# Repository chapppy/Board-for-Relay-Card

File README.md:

#  Board-for-Relay-Card
This repository contains design of schematic and PCB for Relay Card. 
**This board support**:
- up to 7 relays (with SPDT contacts)
- additional 7 relays on extra board
- control of relay over USB
- control of relay over CAN
- single power supply from USB
- possibility of external power supply (for board control over CAN)

This is based on STM32 microcontroller F0 family (STM32F072C8T6). This microcontroller supports USB and in advance it support crystal-less USB. The CAN driver is also available. 

The goal is use as less parts as possible with consideration of hand soldering. All the part should be simple to get or replace with another compatible. The design is simple two layer board with most of the parts (and all necessary) on top layer. The design fits to box for DIN lath.

This is related to these repositories:
[Firmware-for-Relay-Card](https://github.com/chapppy/Firmware-for-Relay-Card "Firmware-for-Relay-Card") 
[Sample-GUI-for-Relay-Card](https://github.com/chapppy/Sample-GUI-for-Relay-Card "Sample-GUI-for-Relay-Card")
[Board-for-Relay-Card](https://github.com/chapppy/Board-for-Relay-Card "Board-for-Relay-Card")

## schematic
[full schematic](https://github.com/chapppy/Board-for-Relay-Card/blob/master/export/schematic-full.pdf "full schematic")

In case of control only over USB and 4 relays, there is reduced schematic:
[reduced schematic](https://github.com/chapppy/Board-for-Relay-Card/blob/master/export/schematic-USB-4-rleays.pdf "reduced schematic")

## PCB design

## data for manufacturing
[manufacturing data](https://github.com/chapppy/Board-for-Relay-Card/blob/master/export/manufacturing.zip "manufacturing data")

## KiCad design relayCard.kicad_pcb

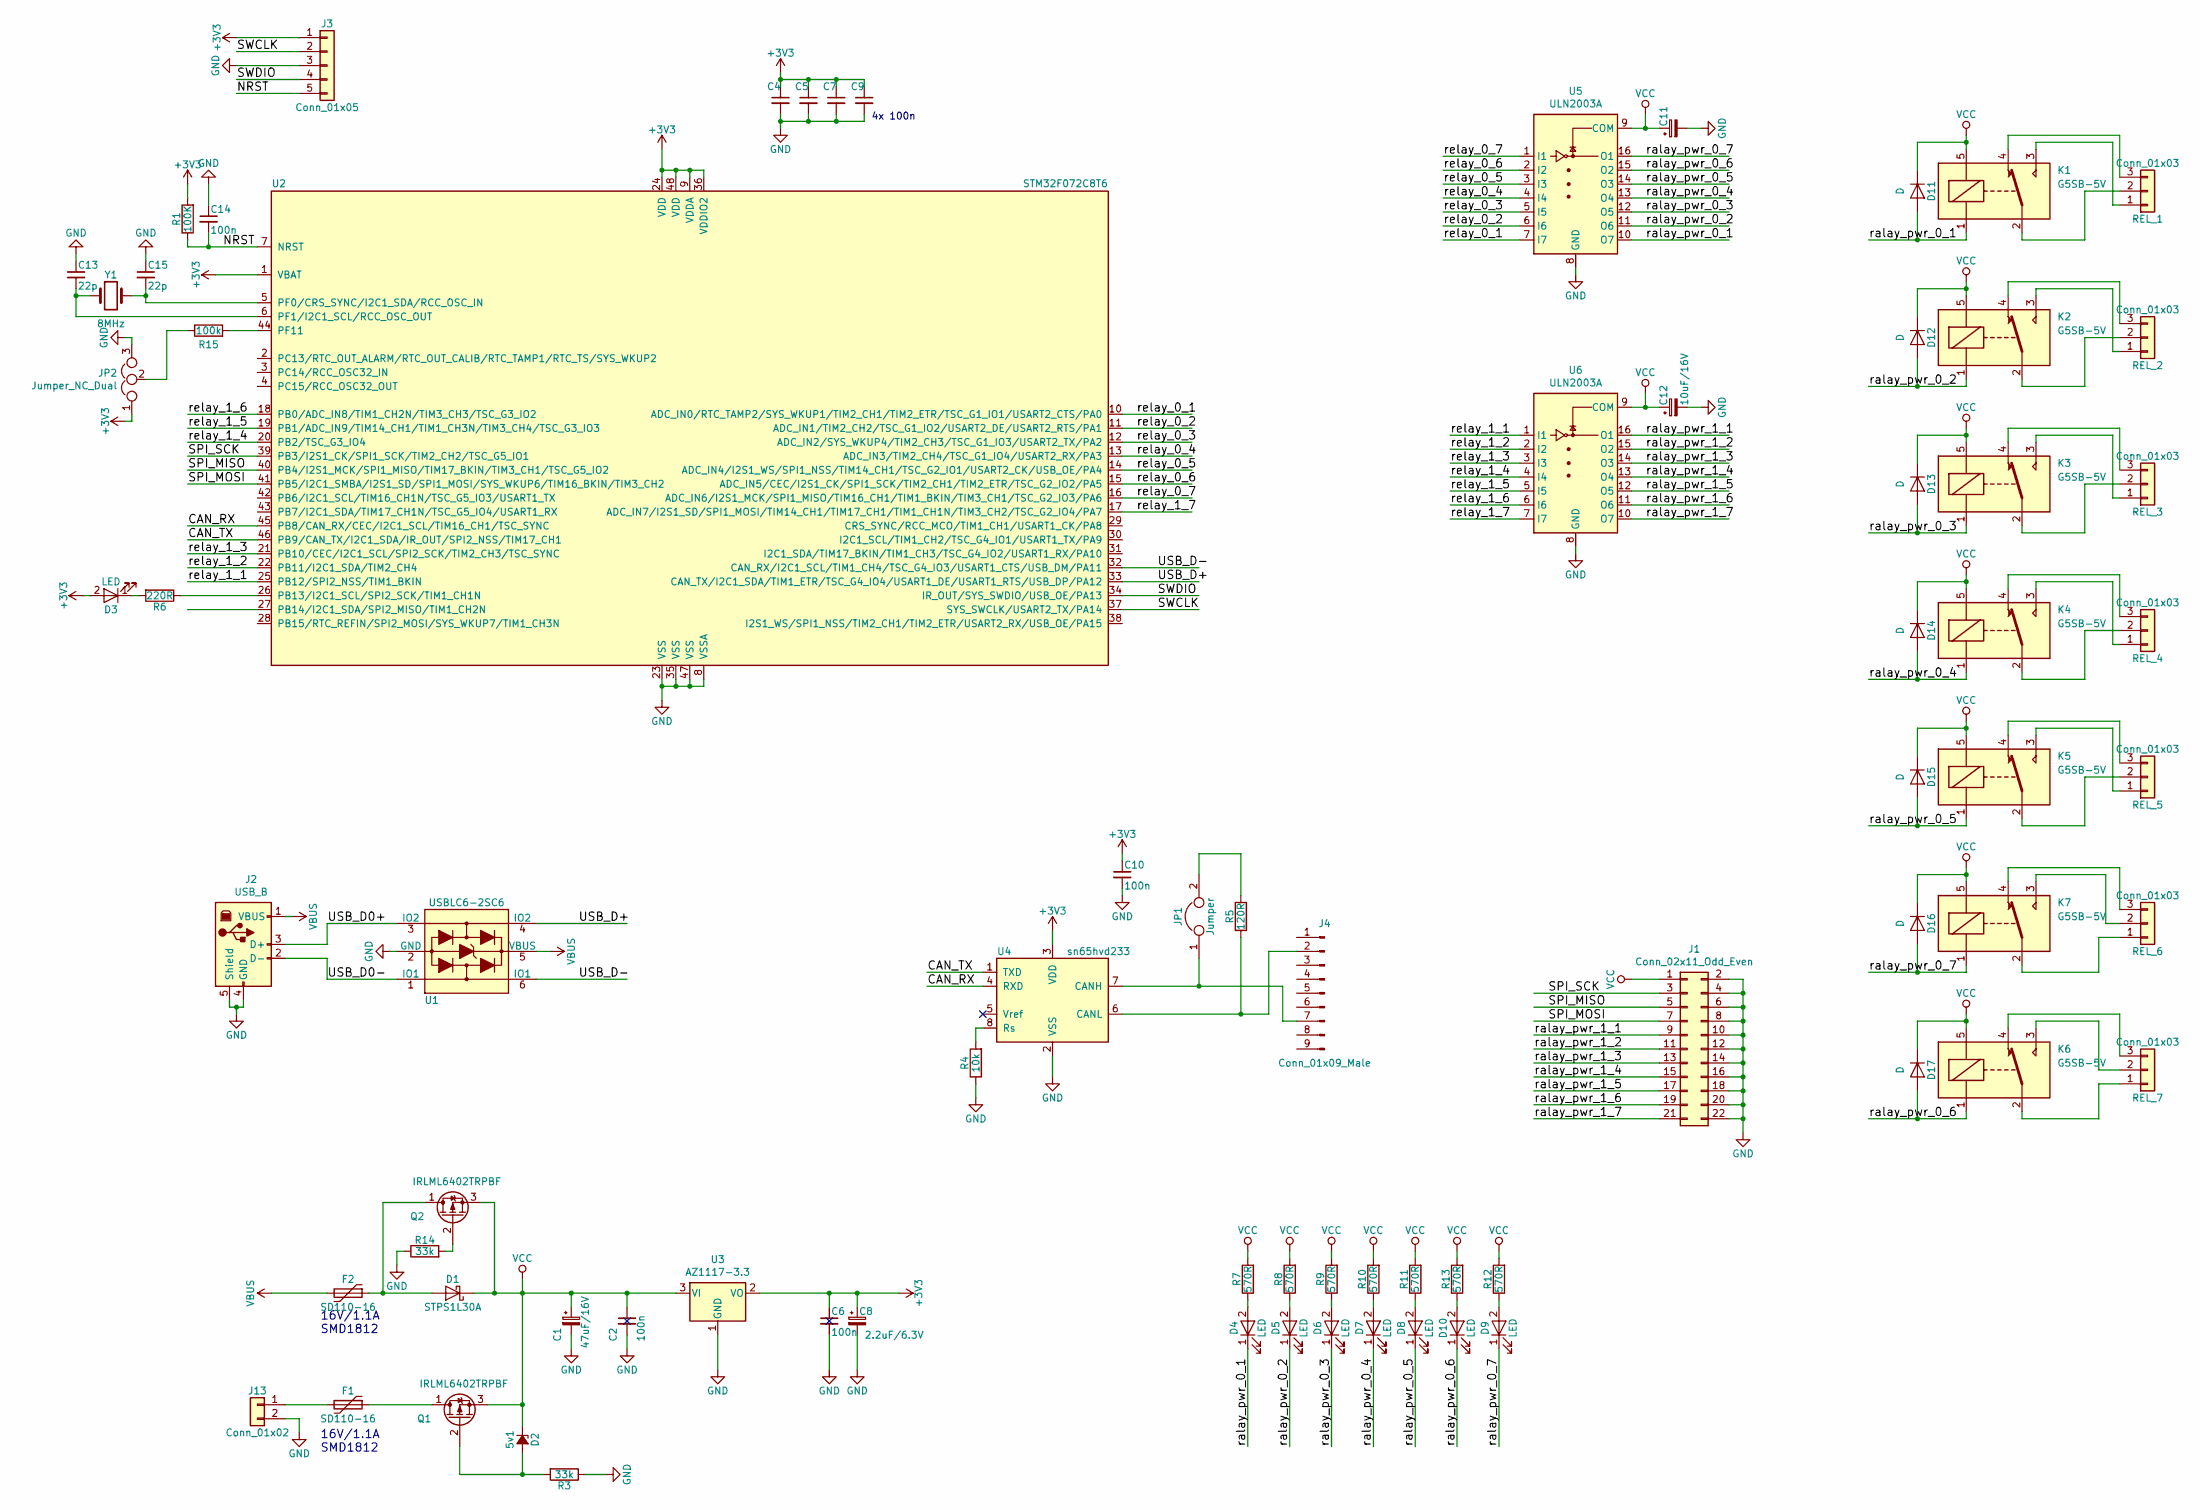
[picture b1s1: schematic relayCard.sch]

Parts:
C1: 47uF/16V; CP_Tantalum_Case-C_EIA-6032-28_Hand
C2, C4, C5, C6, C7, C9, C10, C14: 100n; C_0805_HandSoldering
C8: 2.2uF/6.3V; CP_Tantalum_Case-A_EIA-3216-18_Hand
C11, C12: 10uF/16V; CP_Tantalum_Case-B_EIA-3528-21_Hand
C13, C15: 22p; C_0805_HandSoldering
D1: STPS1L30A; D_SMA
D2: 5v1; D_SOD-323
D3, D4, D5, D6, D7, D8, D9, D10: LED; D_0805
D11: D; D_SOD-323
D12, D13, D14, D15, D16, D17: D; D_SOD-123
F1, F2: SD110-16; R_1812_HandSoldering
J1: Conn_02x11_Odd_Even; Pin_Header_Straight_2x11_Pitch2.54mm
J2: USB_B
J3: Conn_01x05; Pin_Header_Straight_1x05_Pitch2.54mm
J4: Conn_01x09_Male; DSUB-9_Female_Horizontal_Pitch2.77x2.84mm_EdgePinOffset7.70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
J13: Conn_01x02; TerminalBlock_bornier-2_P5.08mm
JP1: Jumper; Pin_Header_Straight_1x02_Pitch2.54mm
JP2: Jumper_NC_Dual; Pin_Header_Straight_1x03_Pitch2.54mm
K1, K2, K3, K4, K5, K6, K7: G5SB-5V; Relay_SPDT_OMRON-G5Q
Q1, Q2: IRLML6402TRPBF; SOT-23
R1: 100K; R_0805_HandSoldering
R3, R14: 33k; R_0805_HandSoldering
R4: 10k; R_0805_HandSoldering
R5: 120R; R_0805_HandSoldering
R6: 220R; R_0805_HandSoldering
R7, R8, R9, R10, R11, R12, R13: 570R; R_0805_HandSoldering
R15: 100k; R_0805_HandSoldering
REL_1, REL_2, REL_3, REL_4, REL_5, REL_6, REL_7: Conn_01x03; TerminalBlock_bornier-3_P5.08mm
U1: USBLC6-2SC6; SOT-23-6
U2: STM32F072C8T6; LQFP-48_7x7mm_Pitch0.5mm
U3: AZ1117-3.3; SOT-223
U4: sn65hvd233; SOIC-8_3.9x4.9mm_Pitch1.27mm
U5, U6: ULN2003A; SOIC-16_3.9x9.9mm_Pitch1.27mm
Y1: 8MHz; Crystal_HC49-4H_Vertical

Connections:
+3V3: C4.1, C5.1, C6.1, C7.1, C8.1, C9.1, C10.1, D3.2 (A), J3.1, JP2.1, R1.2, U2.1 (VBAT), U2.9 (VDDA), U2.24 (VDD), U2.36 (VDDIO2), U2.48 (VDD), U3.2 (VO), U4.3 (VDD)
/CAN_RX: U2.45 (PB8/CAN_RX/CEC/I2C1_SCL/TIM16_CH1/TSC_S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), U4.4 (RXD)
/CAN_TX: U2.46 (PB9/CAN_TX/I2C1_SDA/IR_OUT/SPI2_NSS/TIM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), U4.1 (TXD)
/NRST: C14.2, J3.5, R1.1, U2.7 (NRST)
/SPI_MISO: J1.5, U2.40 (PB4/I2S1_MCK/SPI1_MISO/TIM17_BKIN/TIM3_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)
/SPI_MOSI: J1.7, U2.41 (PB5/I2C1_SMBA/I2S1_SD/SPI1_MOSI/SYS_WKU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)
/SPI_SCK: J1.3, U2.39 (PB3/I2S1_CK/SPI1_SCK/TIM2_CH2/TSC_G5_IO1)
/SWCLK: J3.2, U2.37 (SYS_SWCLK/USART2_TX/PA14)
/SWDIO: J3.4, U2.34 (IR_OUT/SYS_SWDIO/USB_OE/PA13)
/USB_D0+: J2.3 (D+), U1.3 (IO2)
/USB_D0-: J2.2 (D-), U1.1 (IO1)
/USB_D+: U1.4 (IO2), U2.33 (CAN_TX/I2C1_SDA/TIM1_ETR/TSC_G4_IO4/USA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)
/USB_D-: U1.6 (IO1), U2.32 (CAN_RX/I2C1_SCL/TIM1_CH4/TSC_G4_IO3/USA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)
/ralay_pwr_0_1: D4.1 (K), D11.2 (A), K1.1, U5.10 (O7)
/ralay_pwr_0_2: D5.1 (K), D12.2 (A), K2.1, U5.11 (O6)
/ralay_pwr_0_3: D6.1 (K), D13.2 (A), K3.1, U5.12 (O5)
/ralay_pwr_0_4: D7.1 (K), D14.2 (A), K4.1, U5.13 (O4)
/ralay_pwr_0_5: D8.1 (K), D15.2 (A), K5.1, U5.14 (O3)
/ralay_pwr_0_6: D10.1 (K), D17.2 (A), K6.1, U5.15 (O2)
/ralay_pwr_0_7: D9.1 (K), D16.2 (A), K7.1, U5.16 (O1)
/ralay_pwr_1_1: J1.9, U6.16 (O1)
/ralay_pwr_1_2: J1.11, U6.15 (O2)
/ralay_pwr_1_3: J1.13, U6.14 (O3)
/ralay_pwr_1_4: J1.15, U6.13 (O4)
/ralay_pwr_1_5: J1.17, U6.12 (O5)
/ralay_pwr_1_6: J1.19, U6.11 (O6)
/ralay_pwr_1_7: J1.21, U6.10 (O7)
/relay_0_1: U2.10 (ADC_IN0/RTC_TAMP2/SYS_WKUP1/TIM2_CH1/TI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), U5.7 (I7)
/relay_0_2: U2.11 (ADC_IN1/TIM2_CH2/TSC_G1_IO2/USART2_DE/U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), U5.6 (I6)
/relay_0_3: U2.12 (ADC_IN2/SYS_WKUP4/TIM2_CH3/TSC_G1_IO3/U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), U5.5 (I5)
/relay_0_4: U2.13 (ADC_IN3/TIM2_CH4/TSC_G1_IO4/USART2_RX/P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), U5.4 (I4)
/relay_0_5: U2.14 (ADC_IN4/I2S1_WS/SPI1_NSS/TIM14_CH1/TSC_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), U5.3 (I3)
/relay_0_6: U2.15 (ADC_IN5/CEC/I2S1_CK/SPI1_SCK/TIM2_CH1/T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), U5.2 (I2)
/relay_0_7: U2.16 (ADC_IN6/I2S1_MCK/SPI1_MISO/TIM16_CH1/TI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), U5.1 (I1)
/relay_1_1: U2.25 (PB12/SPI2_NSS/TIM1_BKIN), U6.1 (I1)
/relay_1_2: U2.22 (PB11/I2C1_SDA/TIM2_CH4), U6.2 (I2)
/relay_1_3: U2.21 (PB10/CEC/I2C1_SCL/SPI2_SCK/TIM2_CH3/TSC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), U6.3 (I3)
/relay_1_4: U2.20 (PB2/TSC_G3_IO4), U6.4 (I4)
/relay_1_5: U2.19 (PB1/ADC_IN9/TIM14_CH1/TIM1_CH3N/TIM3_CH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), U6.5 (I5)
/relay_1_6: U2.18 (PB0/ADC_IN8/TIM1_CH2N/TIM3_CH3/TSC_G3_I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), U6.6 (I6)
/relay_1_7: U2.17 (ADC_IN7/I2S1_SD/SPI1_MOSI/TIM14_CH1/TIM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), U6.7 (I7)
GND: C1.2, C2.2, C4.2, C5.2, C6.2, C7.2, C8.2, C9.2, C10.2, C11.2, C12.2, C13.1, C14.1, C15.1, J1.2, J1.4, J1.6, J1.8, J1.10, J1.12, J1.14, J1.16, J1.18, J1.20, J1.22, J2.4 (GND), J2.5 (Shield), J3.3, J13.2, JP2.3, R3.1, R4.1, R14.1, U1.2 (GND), U2.8 (VSSA), U2.23 (VSS), U2.35 (VSS), U2.47 (VSS), U3.1 (GND), U4.2 (VSS), U5.8 (GND), U6.8 (GND)
unnamed: C13.2, U2.6 (PF1/I2C1_SCL/RCC_OSC_OUT), Y1.1
unnamed: C15.2, U2.5 (PF0/CRS_SYNC/I2C1_SDA/RCC_OSC_IN), Y1.2
unnamed: D1.2 (A), F2.1, Q2.1 (D)
unnamed: D2.2 (A), Q1.2 (G), R3.2
unnamed: D3.1 (K), R6.2
unnamed: D4.2 (A), R7.1
unnamed: D5.2 (A), R8.1
unnamed: D6.2 (A), R9.1
unnamed: D7.2 (A), R10.1
unnamed: D8.2 (A), R11.1
unnamed: D9.2 (A), R12.1
unnamed: D10.2 (A), R13.1
unnamed: F1.1, Q1.1 (D)
unnamed: F1.2, J13.1
unnamed: J4.2, R5.1, U4.6 (CANL)
unnamed: J4.7, JP1.1, U4.7 (CANH)
unnamed: JP1.2, R5.2
unnamed: JP2.2, R15.1
unnamed: K1.2, REL_1.2
unnamed: K1.3, REL_1.1
unnamed: K1.4, REL_1.3
unnamed: K2.2, REL_2.2
unnamed: K2.3, REL_2.1
unnamed: K2.4, REL_2.3
unnamed: K3.2, REL_3.2
unnamed: K3.3, REL_3.1
unnamed: K3.4, REL_3.3
unnamed: K4.2, REL_4.2
unnamed: K4.3, REL_4.1
unnamed: K4.4, REL_4.3
unnamed: K5.2, REL_5.2
unnamed: K5.3, REL_5.1
unnamed: K5.4, REL_5.3
unnamed: K6.2, REL_7.1
unnamed: K6.3, REL_7.2
unnamed: K6.4, REL_7.3
unnamed: K7.2, REL_6.1
unnamed: K7.3, REL_6.2
unnamed: K7.4, REL_6.3
unnamed: Q2.2 (G), R14.2
unnamed: R4.2, U4.8 (Rs)
unnamed: R6.1, U2.26 (PB13/I2C1_SCL/SPI2_SCK/TIM1_CH1N)
unnamed: R15.2, U2.44 (PF11)
VBUS: F2.2, J2.1 (VBUS), U1.5 (VBUS)
VCC: C1.1, C2.1, C11.1, C12.1, D1.1 (K), D2.1 (K), D11.1 (K), D12.1 (K), D13.1 (K), D14.1 (K), D15.1 (K), D16.1 (K), D17.1 (K), J1.1, K1.5, K2.5, K3.5, K4.5, K5.5, K6.5, K7.5, Q1.3 (S), Q2.3 (S), R7.2, R8.2, R9.2, R10.2, R11.2, R12.2, R13.2, U3.3 (VI), U5.9 (COM), U6.9 (COM)

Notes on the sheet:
16V/1.1A SMD1812
4x 100n

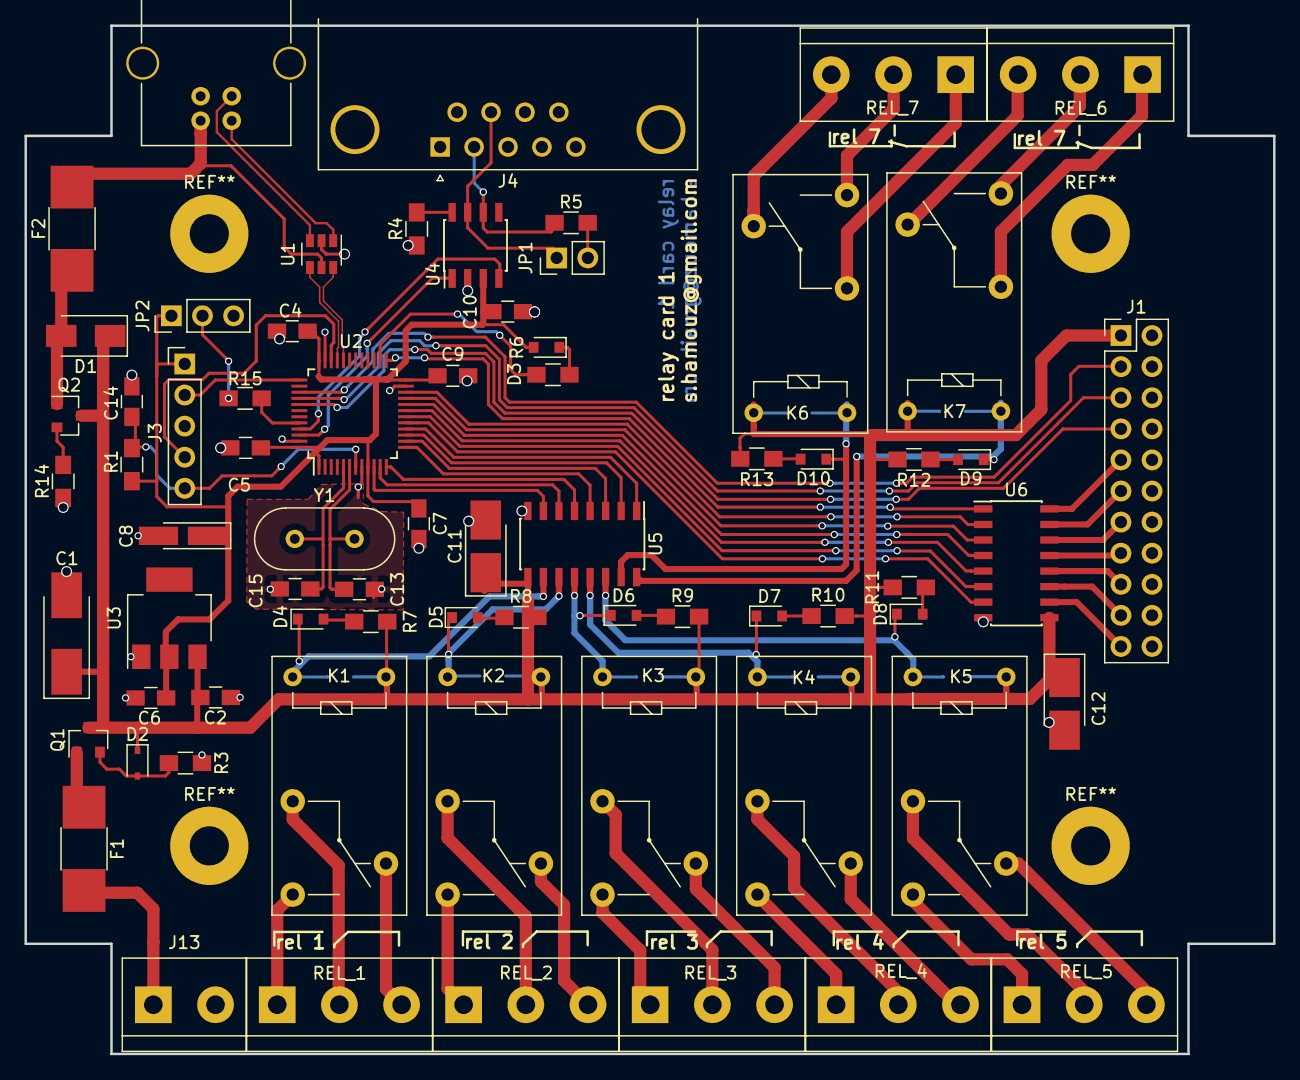
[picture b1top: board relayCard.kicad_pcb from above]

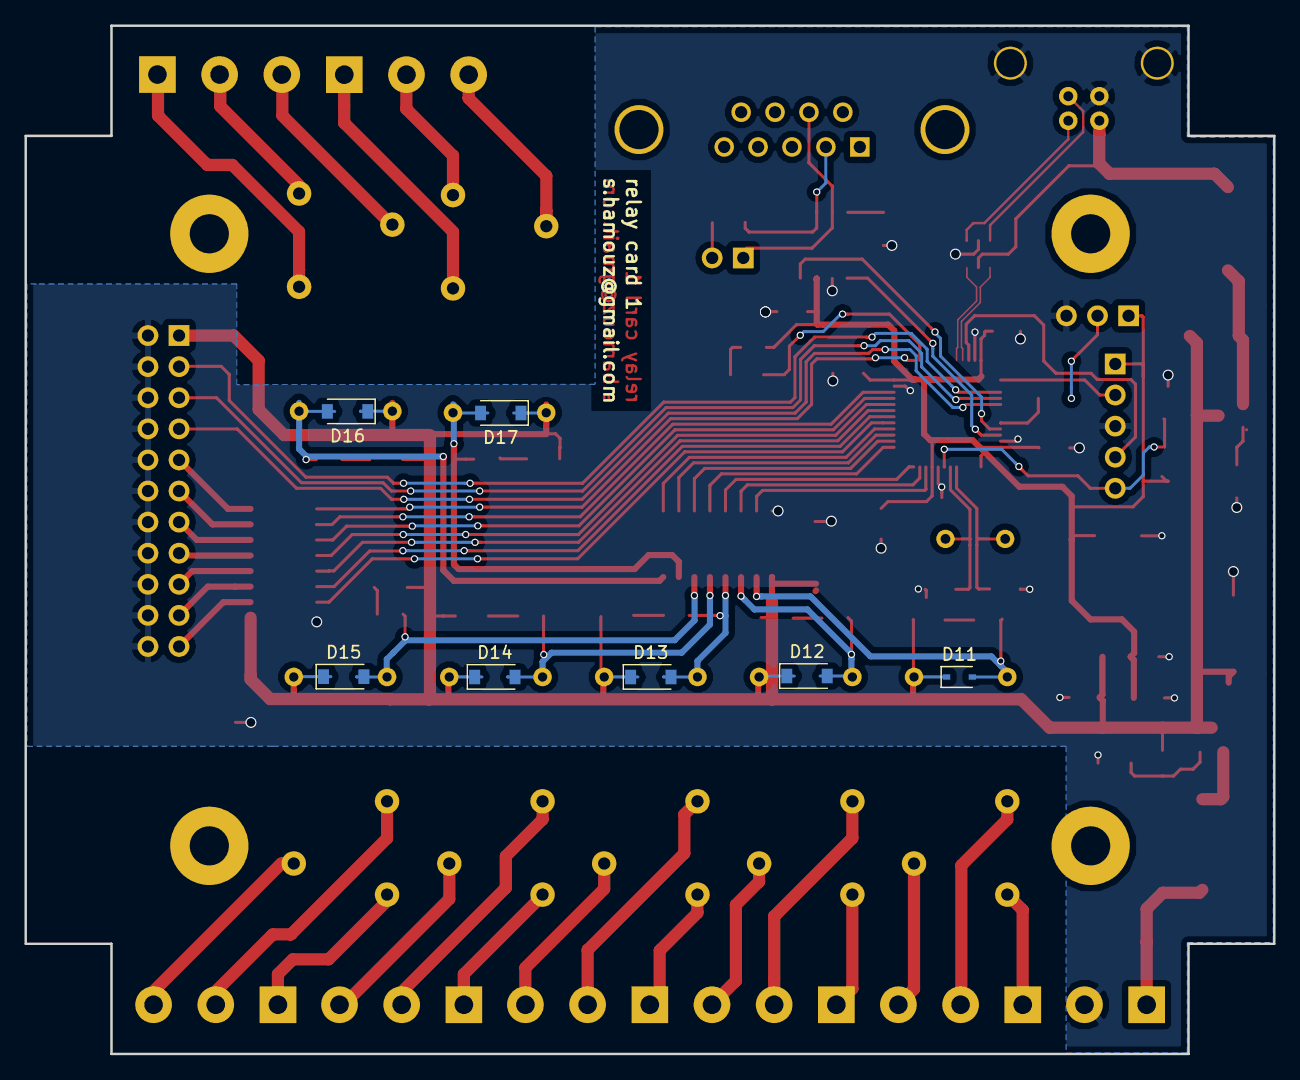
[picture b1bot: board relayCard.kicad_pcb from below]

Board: 2 copper layers, 102.0 x 84.0 mm, 77 parts (7 on the bottom side), 87 nets.

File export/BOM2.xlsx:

quantity | Supplier ref | Link | Designation
8 | 1181041 | https://cz.farnell.com/omron/g5q-1eu-5dc/relay-spdt-250vac-3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 | G5SB-5V
2 | 2112373 | https://cz.farnell.com/multicomp/usb-b-s-ra/usb-2-0-type-b-r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 | USB_B
8 | 1581242 | https://cz.farnell.com/multicomp/mcl-s270gc/led-0805-green-1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 | LED
4 | 498737 | https://cz.farnell.com/avx/tajb106k016rnj/cap-10-f-16v-10-12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 | 10uF/16V
2 | 2750643 | https://cz.farnell.com/stmicroelectronics/stm32f072c8t6/mcu-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 | STM32F042C4Tx
2 | 2852737 | https://cz.farnell.com/avx/tajc476k016snj/cap-47-f-16v-10/dp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 | 47uF/16V
2 | 2321203 | https://cz.farnell.com/kemet/t491a225k006at/cap-2-2-f-6-3v-1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 | 2.2uF/6.3V
2 | 2317476 | https://cz.farnell.com/on-semiconductor/mm3z5v1st1g/diode-ze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 | 5v1
4 | 2468051 | https://cz.farnell.com/infineon/irlml2244trpbf/mosfet-p-ch-2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 | IRLML6402TRPBF
2 | 1269406 | https://cz.farnell.com/stmicroelectronics/usblc6-2sc6/esd-pr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 | USBLC6-2SC6
5 | 2510222 | https://cz.farnell.com/microchip/mic5205-3-3ym5-tr/ic-ldo-15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 | MIC5205-3.3
2 | 1842268 | https://cz.farnell.com/txc/9b-8-000maaj-b/xtal-8-000mhz-18pf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 | 8MHz
2 | 9907491 | https://cz.farnell.com/stmicroelectronics/stps1l30a/diode-sc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 | STPS1L30A
4 | 2335704 | https://cz.farnell.com/texas-instruments/uln2003lvdr/relay-d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 | ULN2003A
2 | 1345924 | https://cz.farnell.com/littelfuse/minismdc075f-24-2/polyswit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 | SD110-16
2 | 1207268 | https://cz.farnell.com/texas-instruments/sn65hvd233dg4/trans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 | sn65hvd233
8 | 8734275 | https://cz.farnell.com/nexperia/bas316-115/diode-switching-2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 | D
2 | 2980894 | https://cz.farnell.com/stmicroelectronics/stm32g071gbu6/mcu-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 | STM32G071GBU6

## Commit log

2019-02-17 first manufactured version
2019-02-18 Created documentation
